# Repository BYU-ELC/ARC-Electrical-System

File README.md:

# ARC-Electrical-System
Electrical System for Autonomous Robotics Competition

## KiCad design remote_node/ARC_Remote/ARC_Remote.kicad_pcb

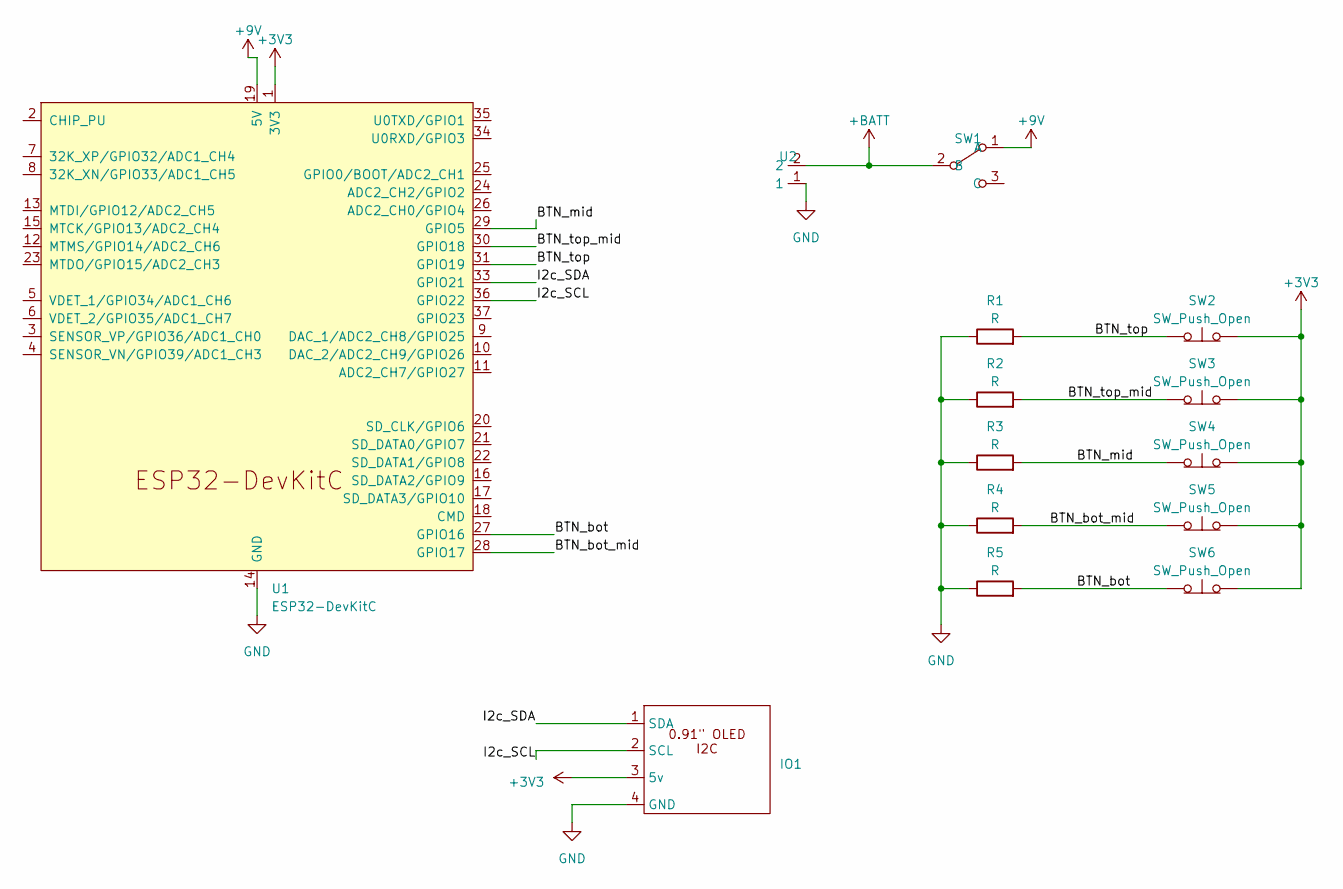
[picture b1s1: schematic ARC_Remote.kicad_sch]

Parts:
IO1: 0.91_OLED_I2C
R1, R2, R3, R4, R5: R; R_Axial_DIN0207_L6.3mm_D2.5mm_P10.16mm_Horizontal
SW1: SPDT_THROUGH_HOLE
SW2, SW3, SW4, SW5, SW6: SW_Push_Open; 2pin button
U1: ESP32-DevKitC
U2: WAGO_SCREW2x1

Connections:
+3V3: IO1.3 (5v), SW2.2 (B), SW3.2 (B), SW4.2 (B), SW5.2 (B), SW6.2 (B), U1.1 (3V3)
+9V: SW1.1 (A), U1.19 (5V)
+BATT: SW1.2 (B), U2.2
/BTN_bot: R5.2, SW6.1 (A), U1.27 (GPIO16)
/BTN_bot_mid: R4.2, SW5.1 (A), U1.28 (GPIO17)
/BTN_mid: R3.2, SW4.1 (A), U1.29 (GPIO5)
/BTN_top: R1.2, SW2.1 (A), U1.31 (GPIO19)
/BTN_top_mid: R2.2, SW3.1 (A), U1.30 (GPIO18)
/I2c_SCL: IO1.2 (SCL), U1.36 (GPIO22)
/I2c_SDA: IO1.1 (SDA), U1.33 (GPIO21)
GND: IO1.4 (GND), R1.1, R2.1, R3.1, R4.1, R5.1, U1.14 (GND), U1.32 (GND), U1.38 (GND), U2.1

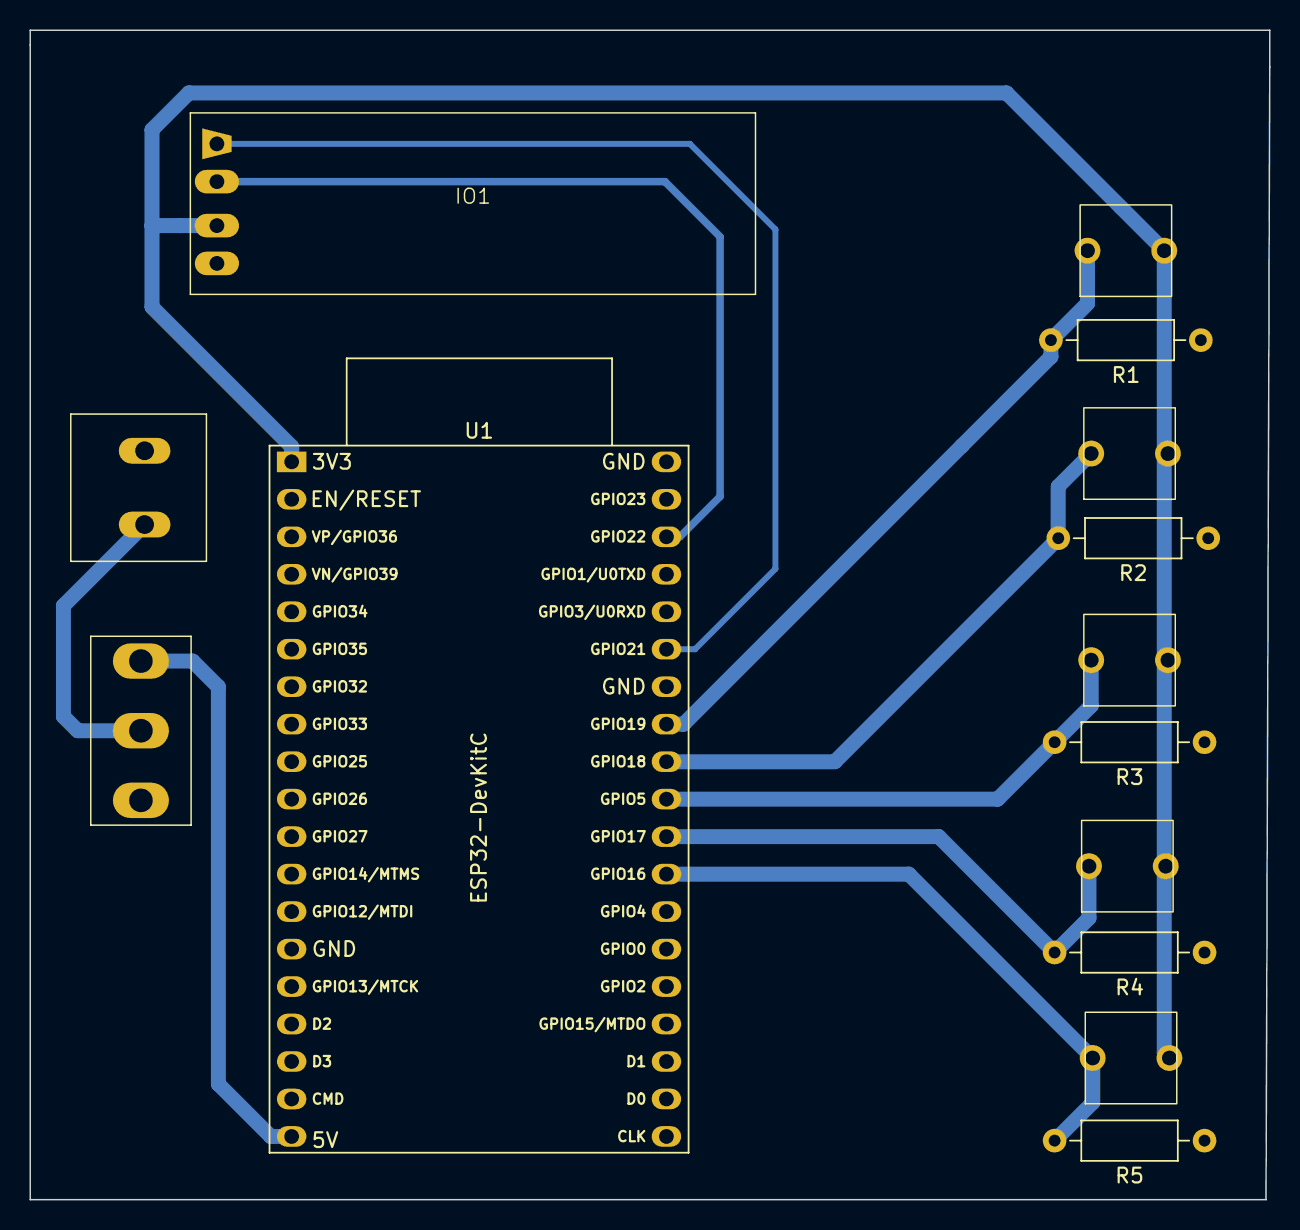
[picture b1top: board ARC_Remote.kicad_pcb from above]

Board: 2 copper layers, 84.0 x 79.2 mm, 14 parts (0 on the bottom side), 11 nets.

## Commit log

2023-11-09 Draft a match state enum
2023-11-15 Added basic directories and prototyping files
2023-12-08 added hardware for the remote
2024-03-25 Notion upload
2024-03-26 Replaced state numbers with macro defintions
2024-03-26 Improved State Change Process
2024-03-26 Peer Names
2024-03-27 Fixed Audio Repeat Bug
2024-03-27 Remote State Change Bug Fixes
2024-03-27 Better Button Debouncing
2024-03-29 Remote now tracks timer with hardware timers millis()
2024-03-29 Node ignores double 1 minute calls
2024-04-02 Timer now syncs with remote, time is rounded up for exact 0:00 end
2024-04-02 Remote sends out time sync
2024-04-02 Fixed Some Time rounding erros
2024-04-02 Housekeeping
2024-04-04 Fixed Duplicate Countdown Bug
2024-04-04 Swapped to new Debounce Library
